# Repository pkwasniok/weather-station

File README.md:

# Weather station

## Sensors

 - Temperature, pressure (BMP280)
 - Particles (PMS5003)

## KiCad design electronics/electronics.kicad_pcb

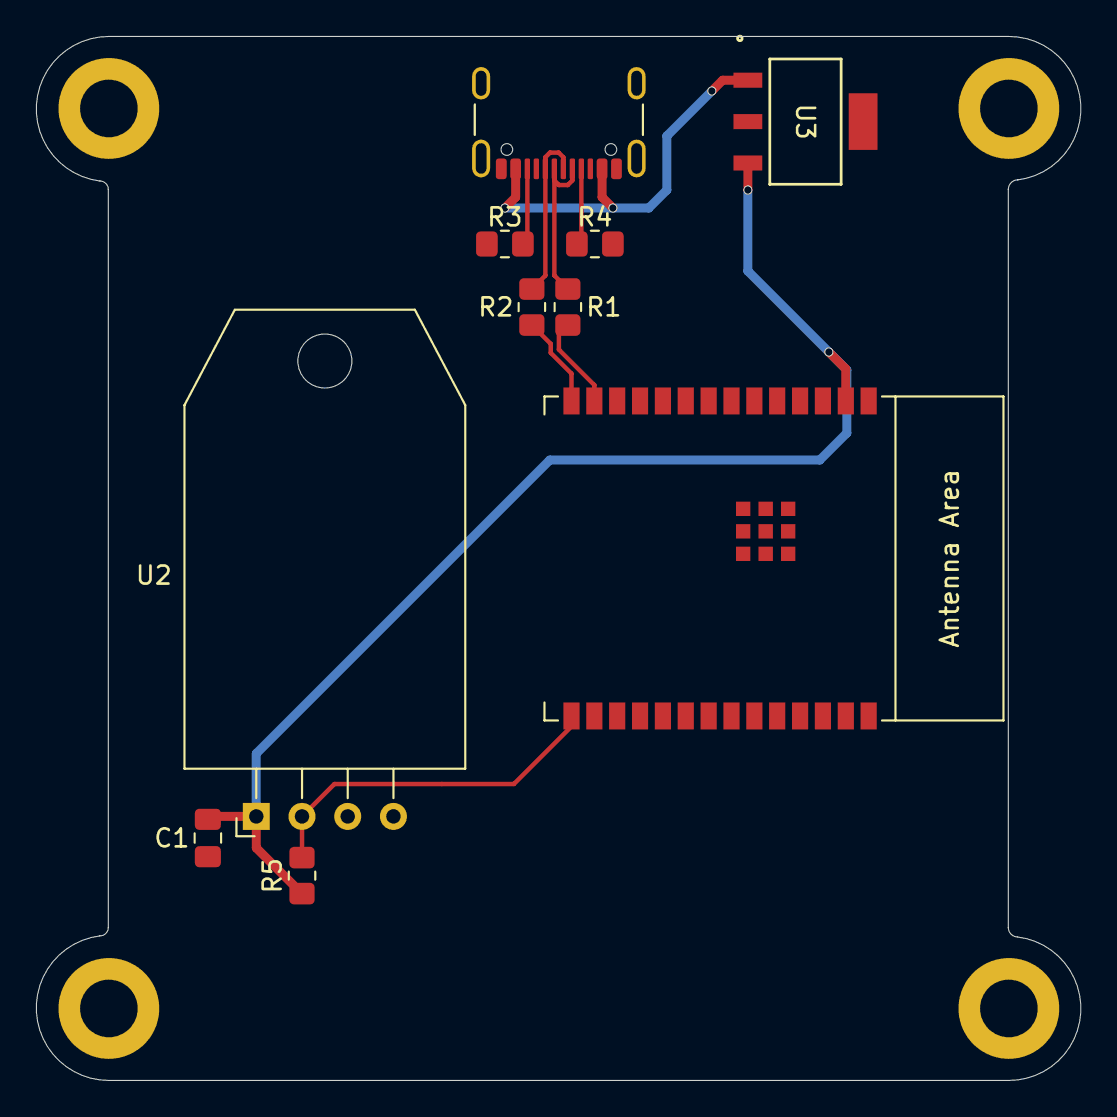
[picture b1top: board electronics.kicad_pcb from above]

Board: 2 copper layers, 58.0 x 58.0 mm, 14 parts (0 on the bottom side), 10 nets.

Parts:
C1: 100C; C_0805_2012Metric_Pad1.18x1.45mm_HandSolder
H1, H2, H3, H4: MountingHole_Pad; MountingHole_3.2mm_M3_DIN965_Pad
J1: USB_C_Receptacle_USB2.0_16P; USB_C_Receptacle_GCT_USB4105-xx-A_16P_TopMnt_Horizontal
R1, R2: 22R; R_0805_2012Metric_Pad1.20x1.40mm_HandSolder
R3, R4: 5.1K; R_0805_2012Metric_Pad1.20x1.40mm_HandSolder
R5: 4.7K; R_0805_2012Metric_Pad1.20x1.40mm_HandSolder
U1: ESP32-C6-WROOM-1
U2: AM2302; ASAIR_AM2302_P2.54mm_Lead2.75mm_TabDown
U3: LM3940IMP-3.3; MP04A

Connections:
+3V3: C1.1, R5.1, U1.2 (3V3), U2.1 (VDD), U3.3 (OUT)
+5V: J1.A4 (VBUS), J1.A9 (VBUS), J1.B4 (VBUS), J1.B9 (VBUS), U3.1 (IN)
AM2302_SDA: R5.2, U1.15 (GPIO9), U2.2 (SDA)
GND: C1.2, H1.1, H2.1, H3.1, H4.1, J1.A1 (GND), J1.A12 (GND), J1.B1 (GND), J1.B12 (GND), J1.S1 (SHIELD), R3.2, R4.2, U1.1 (GND), U1.28 (GND), U1.29 (GND), U2.3 (GND), U2.4 (GND), U3.2 (GND)
unnamed: J1.A5 (CC1), R4.1
unnamed: J1.B5 (CC2), R3.1
unnamed: J1.A6 (D+), J1.B6 (D+), R2.1
unnamed: J1.A7 (D-), J1.B7 (D-), R1.1
USB_D+: R2.2, U1.14 (GPIO13/USB_D+)
USB_D-: R1.2, U1.13 (GPIO12/USB_D-)

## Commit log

2025-09-03 chore: init
2025-09-08 feat: wifi and mqtt
2025-09-08 feat: add pkwasniok/bmp280 component
2025-09-08 feat: temperature and pressure reading
2025-09-12 feat: add enclosure
2025-09-12 cad: finished enclosure
2025-09-13 feat: add pms5003 driver
2025-09-13 feat: tasks
2025-09-15 hardware: add enclosure shell
2025-09-15 hardware: add pcb cutouts
2025-09-15 pcb: add mcu, power regulator and usb-c connector
2025-09-15 pcb: add usb power and data connections
2025-09-15 chore: remove files from vcs
2025-09-15 chore: add enclosure .gitignore
2025-09-15 pcb: add 5.1k pull-downs to usb cc1/cc2
2025-09-15 pcb: add 5.1k pull-downs to usb cc1/cc2 to pcb
2025-09-16 pcb: add am2320
2025-09-21 schematic: add decoupling caps to regulator
2025-09-22 schematic: remade schematic
